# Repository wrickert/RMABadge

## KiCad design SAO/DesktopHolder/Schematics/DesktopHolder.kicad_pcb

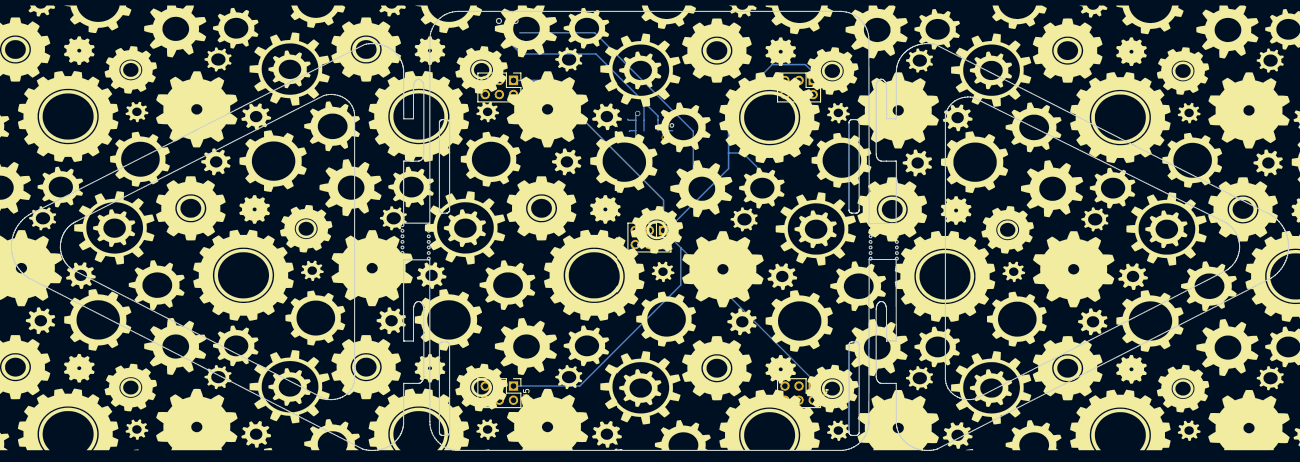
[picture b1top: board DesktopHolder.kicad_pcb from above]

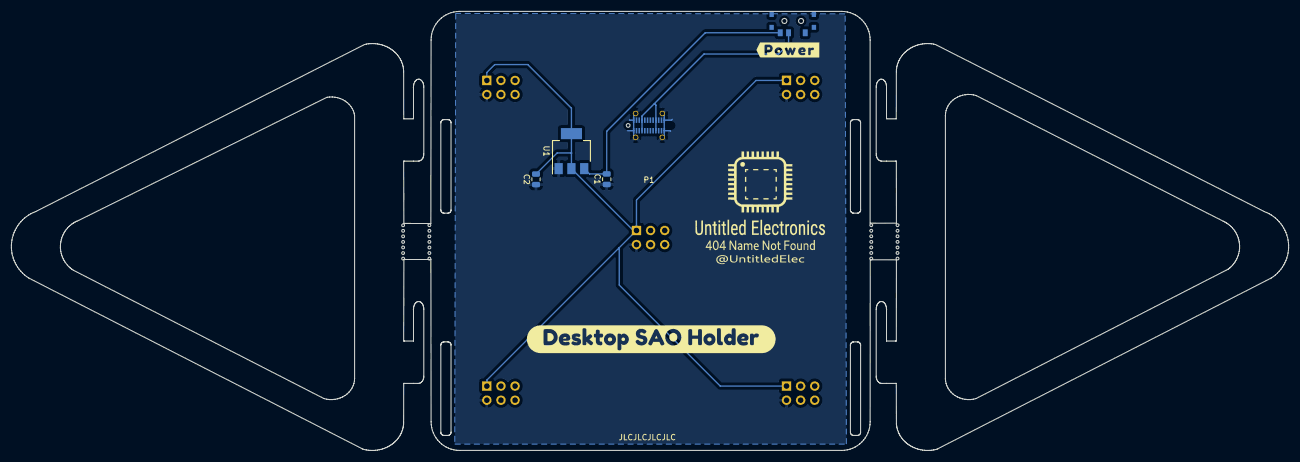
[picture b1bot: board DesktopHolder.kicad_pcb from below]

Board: 2 copper layers, 229.8 x 79.0 mm, 12 parts (7 on the bottom side), 4 nets.

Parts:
C1, C2: 1uF; C_0805_2012Metric
J1, J2, J3, J4, J5: Conn_02x03_Odd_Even; PinHeader_2x03_P2.54mm_Vertical
P1: USB_C_Plug_corrected; Jing_USB-C_Vert_C168703
Power1: SW3; SK-3296S_switch
Ref**: Val**; UELogoAbove
U1: TLV1117-33; SOT-223-3_TabPin2
svg2mod: G***; svg2mod

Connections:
+5V: P1.A4 (VBUS), P1.A9 (VBUS), P1.B4 (VBUS), P1.B9 (VBUS), Power1.2 (B)
unnamed: C1.2, Power1.1 (A), U1.3 (VI)
VCC: C2.2, J1.1, J2.1, J3.1, J4.1, J5.1, U1.2 (VO)
VSS: C1.1, C2.1, J1.2, J2.2, J3.2, J4.2, J5.2, P1.A1 (GND), P1.A12 (GND), P1.B1 (GND), P1.B12 (GND), P1.S1 (SHIELD), U1.1 (GND)

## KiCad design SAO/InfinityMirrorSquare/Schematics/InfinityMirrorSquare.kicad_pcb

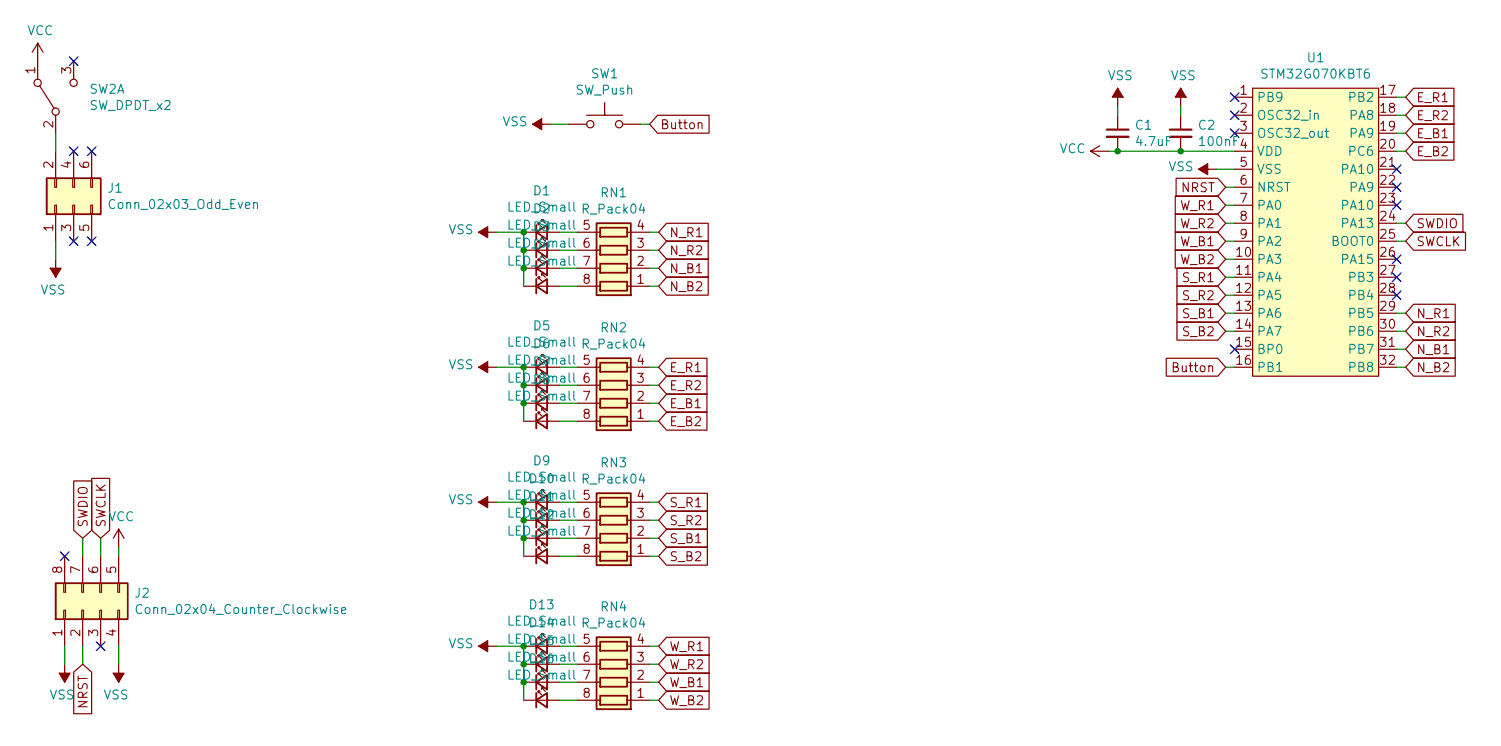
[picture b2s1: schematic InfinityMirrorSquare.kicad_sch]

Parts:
C1: 4.7uF; C_0805_2012Metric
C2: 100nF; C_0805_2012Metric
D1, D2, D3, D4, D5, D6, D7, D8, D9, D10, D11, D12, D13, D14, D15, D16: LED_Small; LED_0603_1608Metric
J1: Conn_02x03_Odd_Even; PinHeader_2x03_P2.54mm_Vertical_SMD
J2: Conn_02x04_Counter_Clockwise; SOIC_clipProgSmall
RN1, RN2, RN3, RN4: R_Pack04; R_Array_Convex_4x0603
SW1: SW_Push; G71-Switch
SW2: SW_DPDT_x2; SK-3296S_switch
U1: STM32G070KBT6; LQFP-32_7x7mm_P0.8mm

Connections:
Button: SW1.2, U1.16 (PB1)
E_B1: RN2.2 (R2.1), U1.19 (PA9)
E_B2: RN2.1 (R1.1), U1.20 (PC6)
E_R1: RN2.4 (R4.1), U1.17 (PB2)
E_R2: RN2.3 (R3.1), U1.18 (PA8)
NRST: J2.2, U1.6 (NRST)
N_B1: RN1.2 (R2.1), U1.31 (PB7)
N_B2: RN1.1 (R1.1), U1.32 (PB8)
N_R1: RN1.4 (R4.1), U1.29 (PB5)
N_R2: RN1.3 (R3.1), U1.30 (PB6)
unnamed: D1.2 (A), RN1.5 (R4.2)
unnamed: D2.2 (A), RN1.6 (R3.2)
unnamed: D3.2 (A), RN1.7 (R2.2)
unnamed: D4.2 (A), RN1.8 (R1.2)
unnamed: D5.2 (A), RN2.5 (R4.2)
unnamed: D6.2 (A), RN2.6 (R3.2)
unnamed: D7.2 (A), RN2.7 (R2.2)
unnamed: D8.2 (A), RN2.8 (R1.2)
unnamed: D9.2 (A), RN3.5 (R4.2)
unnamed: D10.2 (A), RN3.6 (R3.2)
unnamed: D11.2 (A), RN3.7 (R2.2)
unnamed: D12.2 (A), RN3.8 (R1.2)
unnamed: D13.2 (A), RN4.5 (R4.2)
unnamed: D14.2 (A), RN4.6 (R3.2)
unnamed: D15.2 (A), RN4.7 (R2.2)
unnamed: D16.2 (A), RN4.8 (R1.2)
unnamed: J1.2, SW2.2 (B)
SWCLK: J2.6, U1.25 (BOOT0)
SWDIO: J2.7, U1.24 (PA13)
S_B1: RN3.2 (R2.1), U1.13 (PA6)
S_B2: RN3.1 (R1.1), U1.14 (PA7)
S_R1: RN3.4 (R4.1), U1.11 (PA4)
S_R2: RN3.3 (R3.1), U1.12 (PA5)
VCC: C1.2, C2.2, J2.5, SW2.1 (A), U1.4 (VDD)
VSS: C1.1, C2.1, D1.1 (K), D2.1 (K), D3.1 (K), D4.1 (K), D5.1 (K), D6.1 (K), D7.1 (K), D8.1 (K), D9.1 (K), D10.1 (K), D11.1 (K), D12.1 (K), D13.1 (K), D14.1 (K), D15.1 (K), D16.1 (K), J1.1, J2.1, J2.4, SW1.1, U1.5 (VSS)
W_B1: RN4.2 (R2.1), U1.9 (PA2)
W_B2: RN4.1 (R1.1), U1.10 (PA3)
W_R1: RN4.4 (R4.1), U1.7 (PA0)
W_R2: RN4.3 (R3.1), U1.8 (PA1)

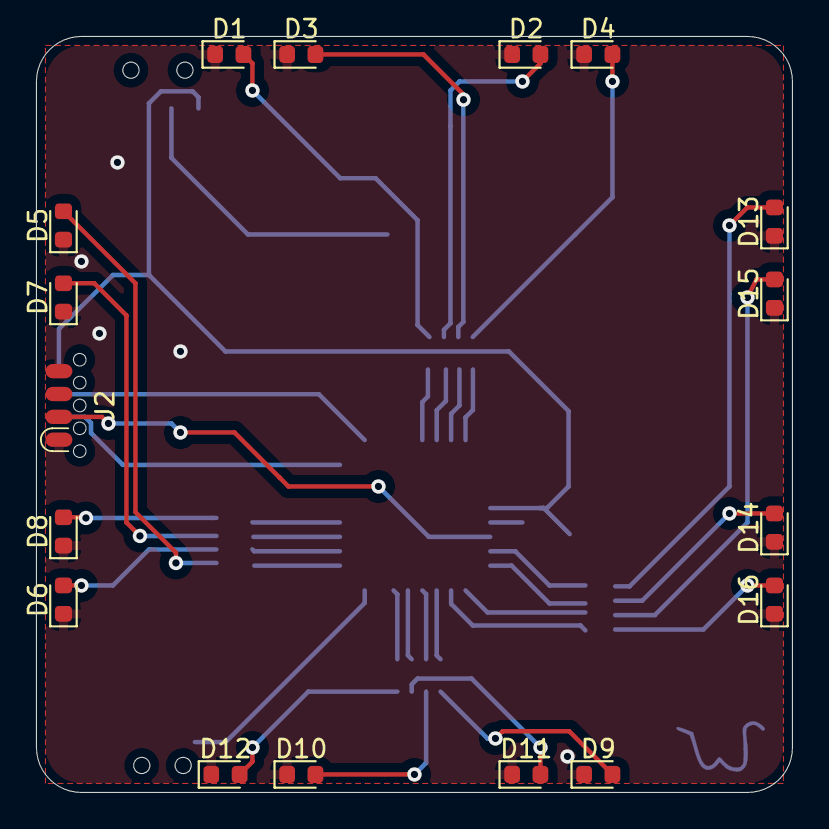
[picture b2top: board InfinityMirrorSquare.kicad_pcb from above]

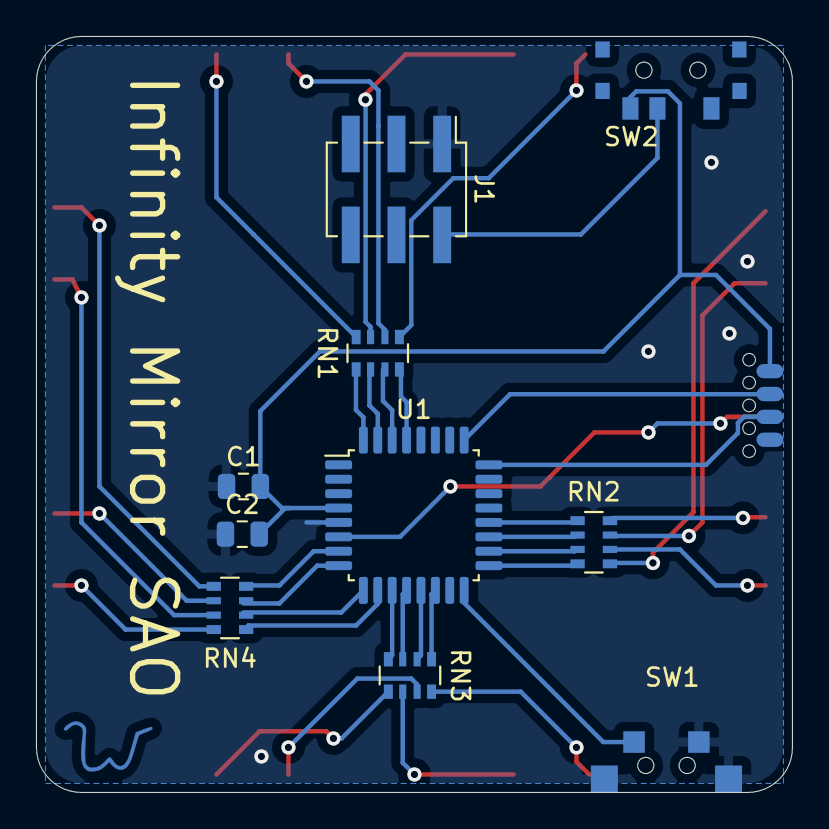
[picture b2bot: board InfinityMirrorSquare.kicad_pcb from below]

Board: 2 copper layers, 42.0 x 42.0 mm, 28 parts (11 on the bottom side), 39 nets.

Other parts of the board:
Ref**: Val**; W

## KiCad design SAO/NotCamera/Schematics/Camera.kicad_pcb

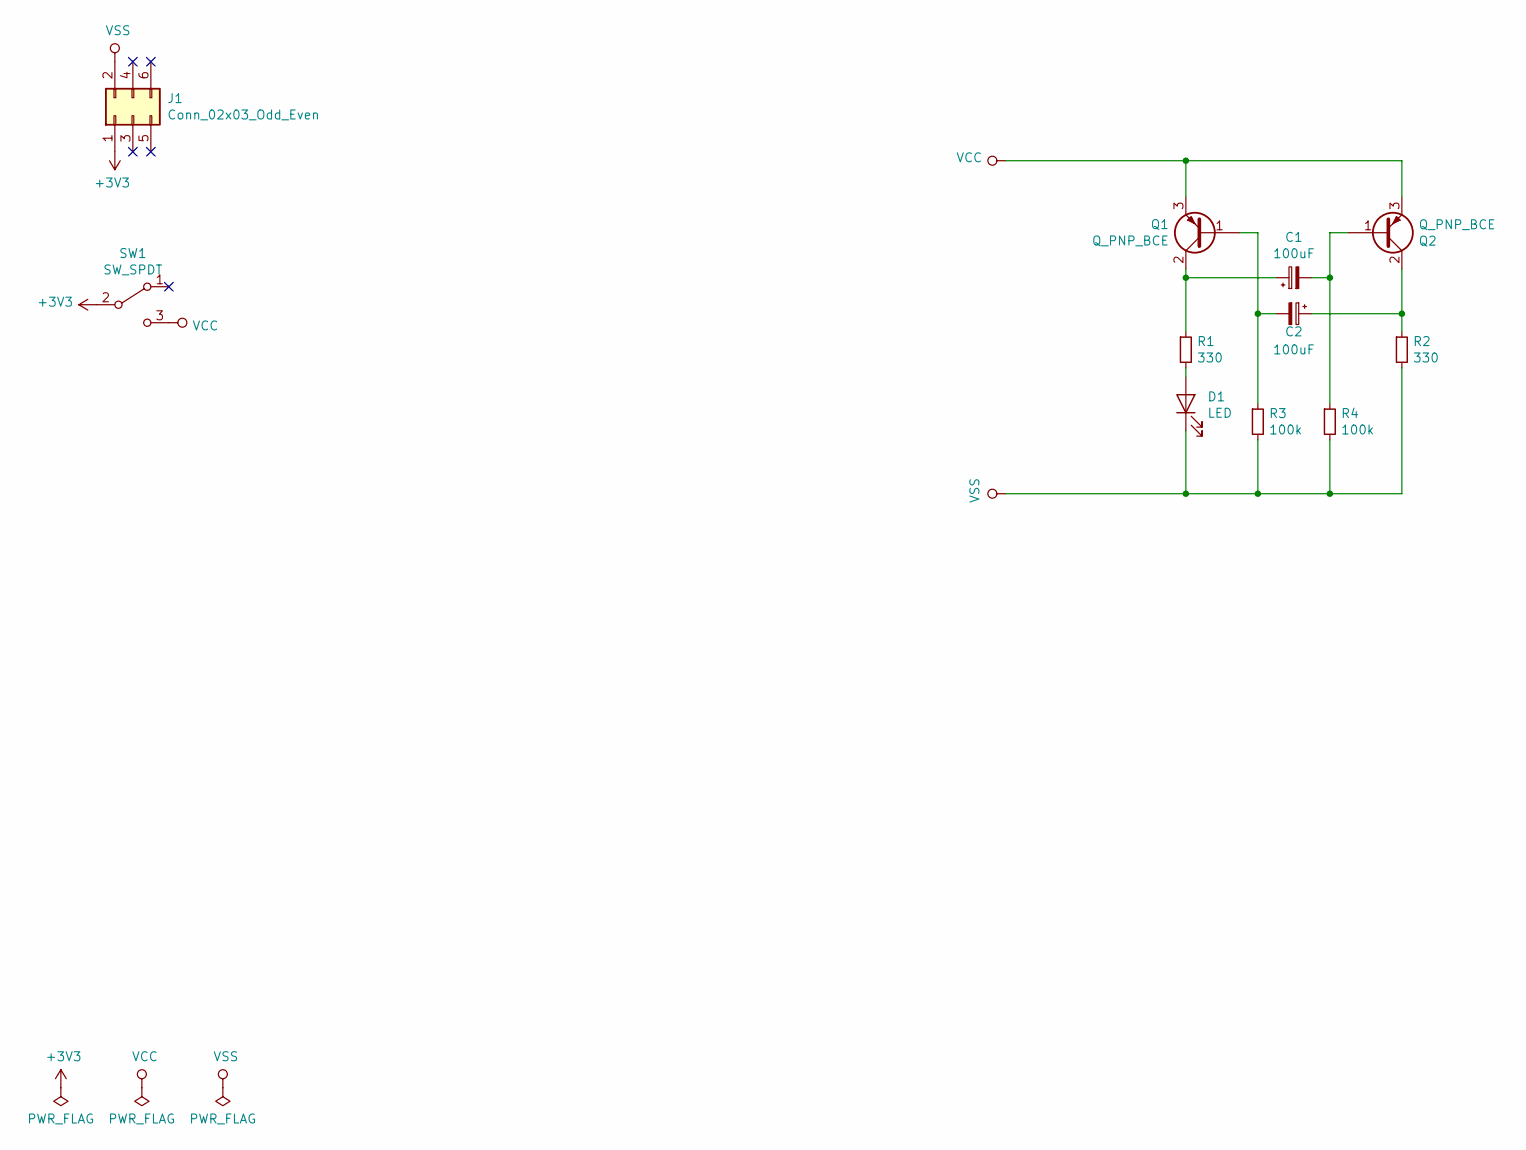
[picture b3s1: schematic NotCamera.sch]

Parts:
C1, C2: 100uF; C_0805_2012Metric
D1: LED; LED_0805_ReverseWithHole
J1: Conn_02x03_Odd_Even; PinHeader_2x03_P2.54mm_Vertical_SMD
Q1, Q2: Q_PNP_BCE; SOT-23
R1, R2: 330; R_0805_2012Metric
R3, R4: 100k; R_0805_2012Metric
SW1: SW_SPDT; SK-3296S_switch

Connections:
+3V3: J1.1, SW1.2 (B); also elsewhere on the board
unnamed: C1.1, Q1.2 (C), R1.1
unnamed: C1.2, Q2.1 (B), R4.1
unnamed: C2.1, Q2.2 (C), R2.1
unnamed: C2.2, Q1.1 (B), R3.1
unnamed: D1.2 (A), R1.2
VCC: Q1.3 (E), Q2.3 (E), SW1.3 (C); also elsewhere on the board
VSS: D1.1 (K), J1.2, R2.2, R3.2, R4.2

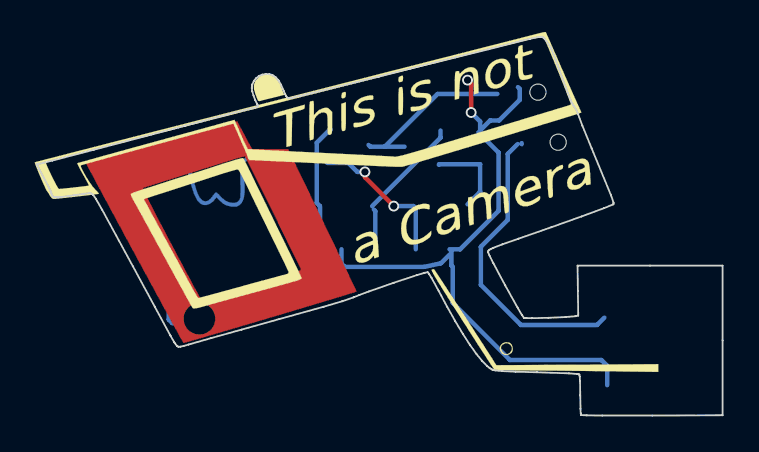
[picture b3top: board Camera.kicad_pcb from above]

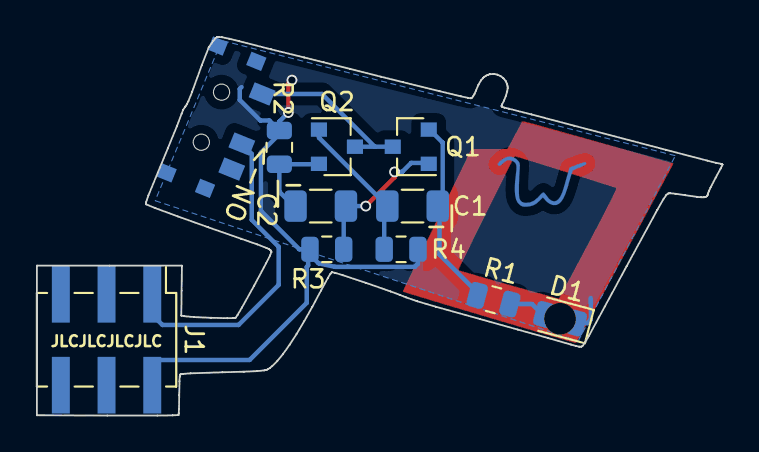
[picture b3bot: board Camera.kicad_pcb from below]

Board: 2 copper layers, 38.1 x 21.0 mm, 13 parts (12 on the bottom side), 8 nets.

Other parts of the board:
ON->: SW_SPDT; SK-3296S_switch
Ref**: Val**; W
Ref**#2: Val**; Camera

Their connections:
+3V3: ON->.2; also elsewhere on the board
VCC: ON->.3; also elsewhere on the board

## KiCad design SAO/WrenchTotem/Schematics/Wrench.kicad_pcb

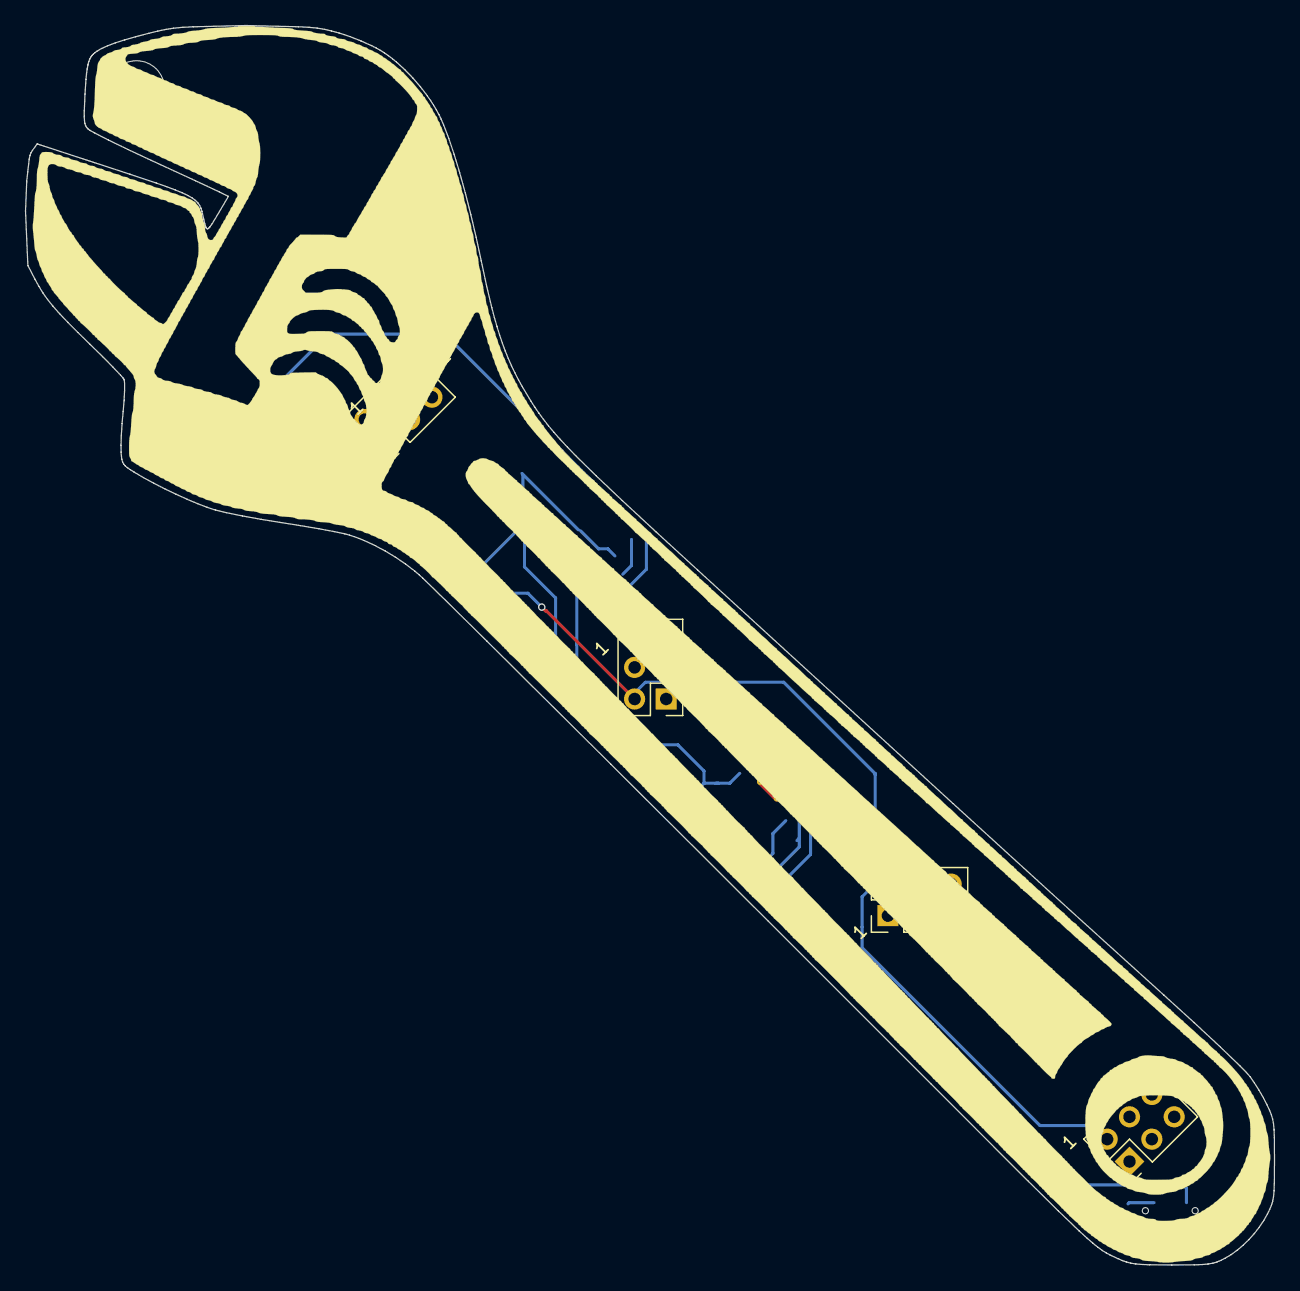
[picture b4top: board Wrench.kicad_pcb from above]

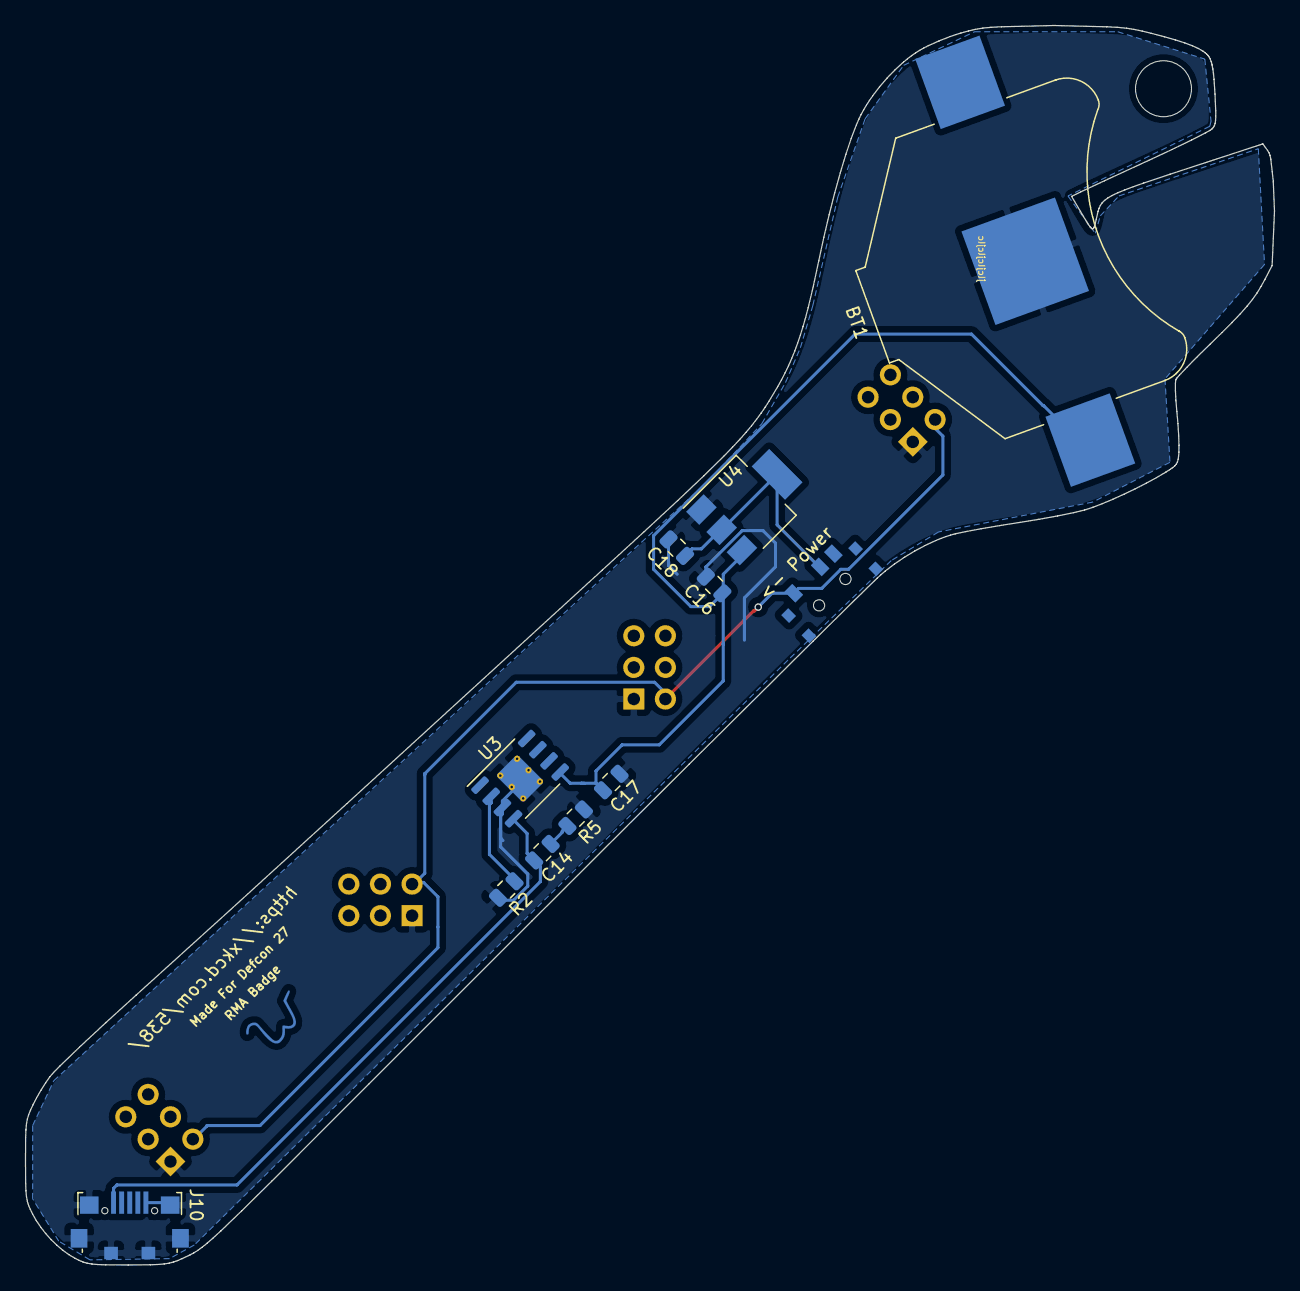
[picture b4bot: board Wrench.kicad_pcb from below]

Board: 2 copper layers, 100.4 x 99.6 mm, 16 parts (12 on the bottom side), 7 nets.

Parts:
<- Power: SW_SPDT; SK-3296S_switch
BT1: Battery_Cell; BatteryHolder_Keystone_3008_1x2450
C14, C17: 10uF; C_0805_2012Metric
C16, C18: 1uF; C_0805_2012Metric
J1, J2, J3, J4: Conn_02x03_Odd_Even; PinHeader_2x03_P2.54mm_Vertical
J10: USB_B_Micro; USB_Micro-B_Jing
R2: 1k; R_0805_2012Metric
R5: 1.5; R_0805_2012Metric
Ref**: Val**; W
U3: HX4056; HSOP-8-1EP_3.9x4.9mm_P1.27mm_EP2.41x3.1mm_ThermalVias
U4: TLV1117-33; SOT-223-3_TabPin2

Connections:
+3V3: <- Power.2, C18.1, U4.2
unnamed: C14.1, R5.2
unnamed: C14.2, J10.1, U3.4
unnamed: R2.1, U3.2
VDD: <- Power.3, J1.2, J2.2, J3.2, J4.2
VDDA: BT1.1, C16.1, C17.2, U3.5, U4.3
VSS: BT1.2, C16.2, C17.1, C18.2, J1.1, J2.1, J3.1, J4.1, J10.5, J10.6, R2.2, R5.1, U3.3, U3.9, U4.1
